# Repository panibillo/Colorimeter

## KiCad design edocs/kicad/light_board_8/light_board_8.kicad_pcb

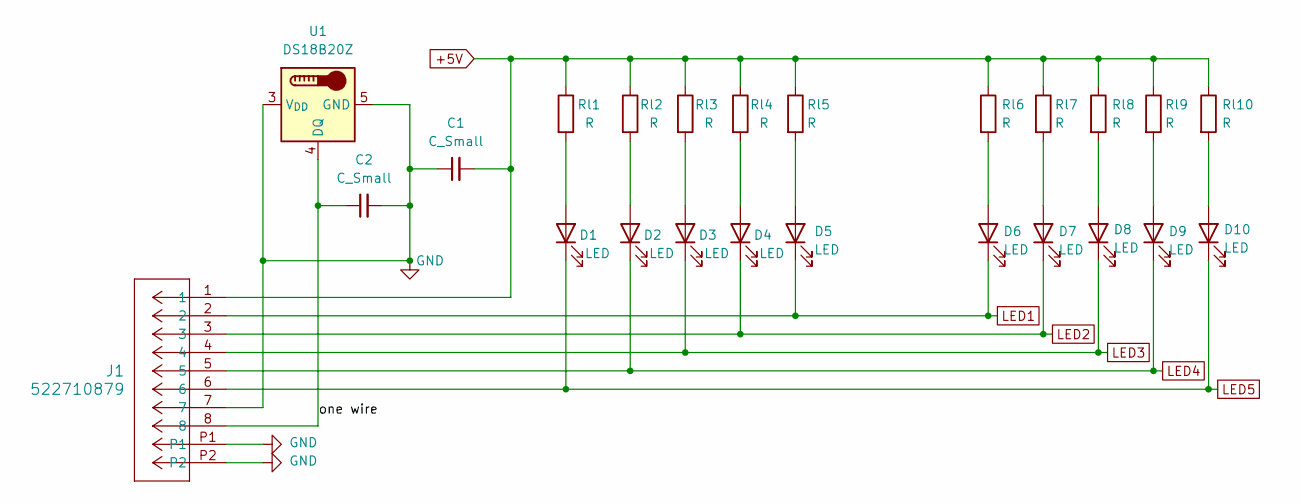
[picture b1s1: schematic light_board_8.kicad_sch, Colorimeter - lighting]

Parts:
C1: C_Small; C_0805_2012Metric
C2: C_Small; C_0603_1608Metric
D1, D2, D3, D4, D5, D6, D7, D8, D9, D10: LED; LED_PLCC_2835
J1: 522710879; CON_522710879_MOL
Rl1, Rl2, Rl3, Rl4, Rl5, Rl6, Rl7, Rl8, Rl9, Rl10: R; R_1206_3216Metric
U1: DS18B20Z; SOIC-8_3.9x4.9mm_P1.27mm

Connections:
+5V: C1.2, J1.1, Rl1.1, Rl2.1, Rl3.1, Rl4.1, Rl5.1, Rl6.1, Rl7.1, Rl8.1, Rl9.1, Rl10.1
/one wire: C2.1, J1.8, U1.4 (DQ)
GND: C1.1, C2.2, J1.7, J1.P1, J1.P2, U1.3 (V_{DD}), U1.5 (GND)
LED1: D5.1 (K), D6.1 (K), J1.2
LED2: D4.1 (K), D7.1 (K), J1.3
LED3: D3.1 (K), D8.1 (K), J1.4
LED4: D2.1 (K), D9.1 (K), J1.5
LED5: D1.1 (K), D10.1 (K), J1.6
unnamed: D1.2 (A), Rl1.2
unnamed: D2.2 (A), Rl2.2
unnamed: D3.2 (A), Rl3.2
unnamed: D4.2 (A), Rl4.2
unnamed: D5.2 (A), Rl5.2
unnamed: D6.2 (A), Rl6.2
unnamed: D7.2 (A), Rl7.2
unnamed: D8.2 (A), Rl8.2
unnamed: D9.2 (A), Rl9.2
unnamed: D10.2 (A), Rl10.2

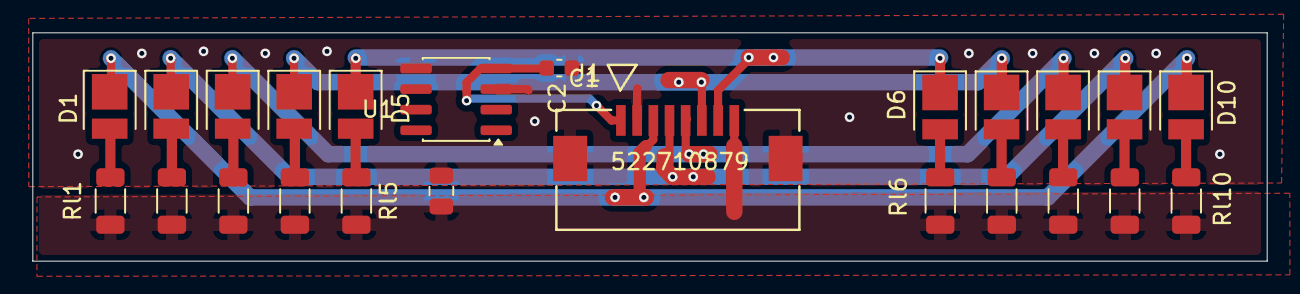
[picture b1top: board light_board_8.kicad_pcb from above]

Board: 2 copper layers, 76.2 x 14.1 mm, 24 parts (0 on the bottom side), 18 nets.

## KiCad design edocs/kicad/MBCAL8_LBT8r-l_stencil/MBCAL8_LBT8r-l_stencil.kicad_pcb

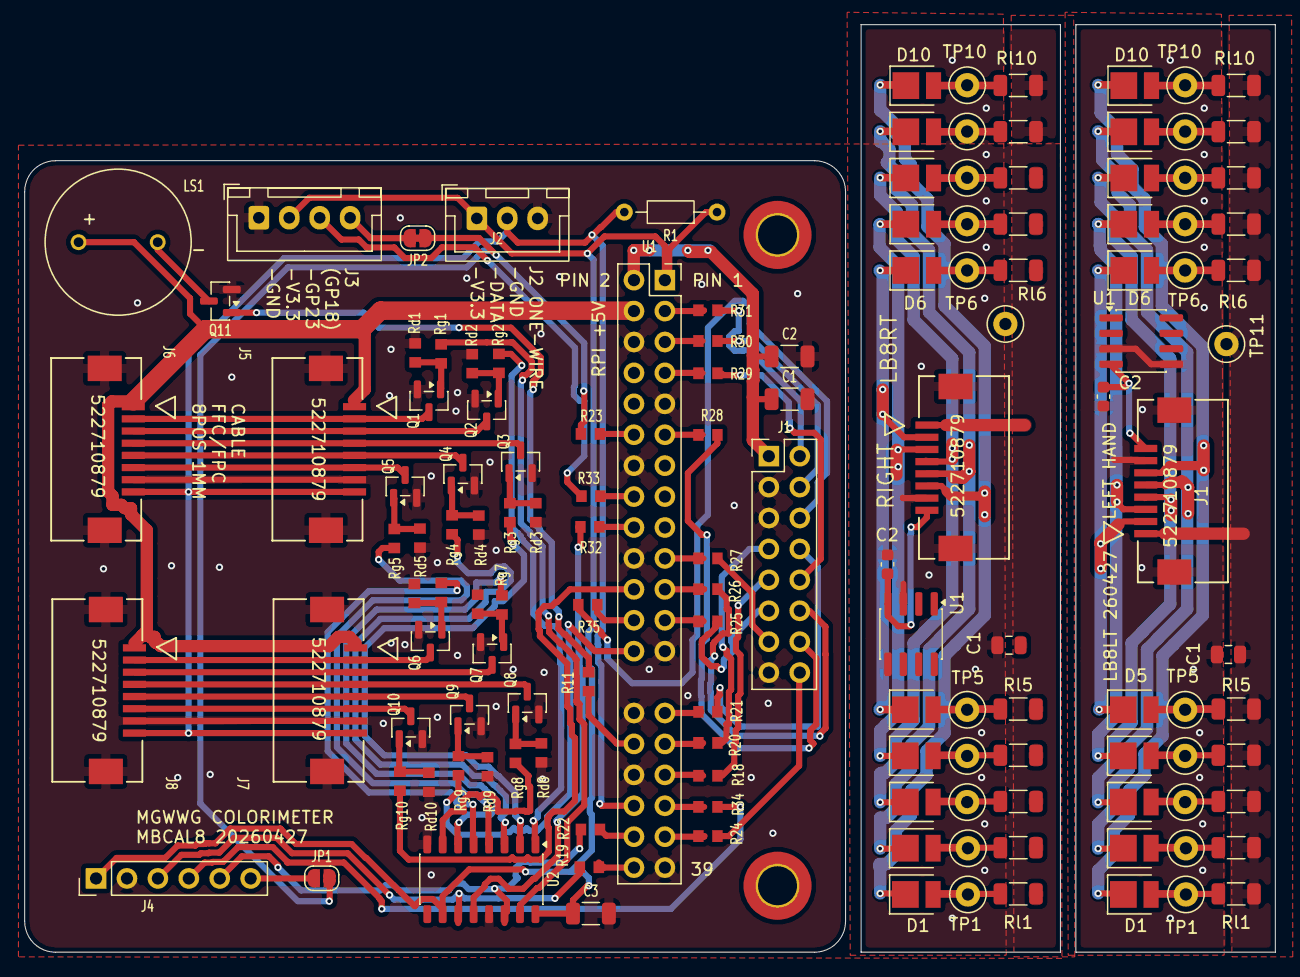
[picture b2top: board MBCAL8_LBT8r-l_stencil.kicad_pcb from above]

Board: 2 copper layers, 102.7 x 76.2 mm, 137 parts (0 on the bottom side), 87 nets.

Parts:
C1, C1#2: C_Small; C_0805_2012Metric
C1#3: 10uf Tant; C_1206_3216Metric
C2, C2#3: C_Small; C_0603_1608Metric
C2#2, C3: 100nF Ceramic; C_1206_3216Metric
D1, D1#2, D2, D2#2, D3, D3#2, D4, D4#2, D5, D5#2, D6, D6#2, D7, D7#2, D8, D8#2, D9, D9#2, D10, D10#2: LED; LED_PLCC_2835
J1: Conn_02x08_Odd_Even; PinHeader_2x08_P2.54mm_Vertical
J1#2, J1#3, J5, J6, J7, J8: 522710879; CON_522710879_MOL
J2: Conn_01x03_Socket; JST_XH_B3B-XH-A_1x03_P2.50mm_Vertical
J3: Conn_01x04_Socket; JST_XH_B4B-XH-A_1x04_P2.50mm_Vertical
J4: Conn_01x06; PinHeader_1x06_P2.54mm_Vertical
JP1: SolderJumper_2_Open; SolderJumper-2_P1.3mm_Open_RoundedPad1.0x1.5mm
JP2: SolderJumper_2_Bridged; SolderJumper-2_P1.3mm_Bridged_RoundedPad1.0x1.5mm
LS1: CEM-1203_42_; CUI_CEM-1203_42_
Q1, Q2, Q3, Q4, Q5, Q6, Q7, Q8, Q9, Q10: AO3400A; SOT-23
Q11: MMBT3904; SOT-23
R1: R_axial; R_Axial_DIN0204_L3.6mm_D1.6mm_P7.62mm_Horizontal
R11: 1K; RESC1608X55N
R18, R20, R21, R24, R25, R26, R27, R28, R29, R30, R31, R32, R33, R34, R35: R33; RESC1608X55N
R19, R22, R23: R470; RESC1608X55N
Rd1, Rd2, Rd3, Rd4, Rd5, Rd6, Rd7, Rd8, Rd9, Rd10: 10K; RESC1608X55N
Rg1, Rg2, Rg3, Rg4, Rg5, Rg6, Rg7, Rg8, Rg9, Rg10: 500; RESC1608X55N
Rl1, Rl1#2, Rl2, Rl2#2, Rl3, Rl3#2, Rl4, Rl4#2, Rl5, Rl5#2, Rl6, Rl6#2, Rl7, Rl7#2, Rl8, Rl8#2, Rl9, Rl9#2, Rl10, Rl10#2: R; R_1206_3216Metric
TP1, TP1#2, TP2, TP2#2, TP3, TP3#2, TP4, TP4#2, TP5, TP5#2, TP6, TP6#2, TP7, TP7#2, TP8, TP8#2, TP9, TP9#2, TP10, TP10#2, TP11, TP11#2: TestPoint_Small; TestPoint_Loop_D1.80mm_Drill1.0mm_Beaded
U1: RPi_Zero_W; PinSocket_2x20_P2.54mm_Vertical
U1#2, U1#3: DS18B20Z; SOIC-8_3.9x4.9mm_P1.27mm
U2: 74HC595; JEITA_SOIC-16_3.9x9.9mm_P1.27mm

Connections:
+5V: C1.2, C1#2.2, J1#2.1, J1#3.1, J5.1, J6.1, J7.1, J8.1, LS1.P, Rl1.1, Rl1#2.1, Rl2.1, Rl2#2.1, Rl3.1, Rl3#2.1, Rl4.1, Rl4#2.1, Rl5.1, Rl5#2.1, Rl6.1, Rl6#2.1, Rl7.1, Rl7#2.1, Rl8.1, Rl8#2.1, Rl9.1, Rl9#2.1, Rl10.1, Rl10#2.1, TP11.1 (1_1), TP11#2.1 (1_1), U1.4 (5V_PWR)
/Buzzer_IO: Q11.1 (B), R11.2
/D2-TSIRQ: J1.10, R29.1
/D3-LITE: J1.9, R18.1
/D4-SC CS: J1.8, R21.1
/D9-TFT DC: J1.7, R20.1
/D10-TFT CS: J1.6, R35.2
/ICSP MISO: J1.12, R26.1
/ICSP MOSI: J1.13, R27.1
/ICSP SCK: J1.11, R25.1
/SCL: J1.4, R30.1
/SDA: J1.2, R31.1
/led 1 gate: Q1.1 (G), Rd1.1, Rg1.1
/led 2 gate: Q2.1 (G), Rd2.1, Rg2.1
/led 3 GPIO: Rg3.2, U2.2 (QC)
/led 3 gate: Q3.1 (G), Rd3.1, Rg3.1
/led 4 GPIO: Rg4.2, U2.3 (QD)
/led 4 gate: Q4.1 (G), Rd4.1, Rg4.1
/led 5 GPIO: Rg5.2, U2.4 (QE)
/led 5 gate: Q5.1 (G), Rd5.1, Rg5.1
/led 6 GPIO: Rg6.2, U2.5 (QF)
/led 6 gate: Q6.1 (G), Rd6.1, Rg6.1
/led 7 GPIO: Rg7.2, U2.6 (QG)
/led 7 gate: Q7.1 (G), Rd7.1, Rg7.1
/led 8 GPIO: Rg8.2, U2.7 (QH)
/led 8 gate: Q8.1 (G), Rd8.1, Rg8.1
/led 9 GPIO: Rg9.2, U1.26 (GPIO7_CE1)
/led 9 gate: Q9.1 (G), Rd9.1, Rg9.1
/led 10 GPIO: Rg10.2, U1.22 (GPIO25)
/led 10 gate: Q10.1 (G), Rd10.1, Rg10.1
/one wire: C2.1, C2#3.1, J1#2.8, J1#3.8, U1#2.4 (DQ), U1#3.4 (DQ)
/one-wire: J2.2, J5.8, J6.8, J7.8, J8.8, R1.2, U1.36 (GPIO16_CE2)
GND: C1.1, C1#2.1, C1#3.2, C2.2, C2#2.2, C2#3.2, C3.2, J1.3, J1.5, J1.15, J1#2.7, J1#2.P1, J1#2.P2, J1#3.7, J1#3.P1, J1#3.P2, J2.3, J3.1, J4.2, J5.7, J5.P1, J5.P2, J6.7, J6.P1, J6.P2, J7.7, J7.P1, J7.P2, J8.7, J8.P1, J8.P2, Q1.2 (S), Q2.2 (S), Q3.2 (S), Q4.2 (S), Q5.2 (S), Q6.2 (S), Q7.2 (S), Q8.2 (S), Q9.2 (S), Q10.2 (S), Q11.2 (E), Rd1.2, Rd2.2, Rd3.2, Rd4.2, Rd5.2, Rd6.2, Rd7.2, Rd8.2, Rd9.2, Rd10.2, U1.6 (GND), U1.9 (GND), U1.14 (GND), U1.20 (GND), U1.25 (GND), U1.30 (GND), U1.34 (GND), U1.39 (GND), U1#2.3 (V_{DD}), U1#2.5 (GND), U1#3.3 (V_{DD}), U1#3.5 (GND), U2.8 (GND), U2.13 (~OE)
LED1: D5.1 (K), D5#2.1 (K), D6.1 (K), D6#2.1 (K), J1#2.2, J1#3.2, J5.2, J6.2, Q1.3 (D)
LED2: D4.1 (K), D4#2.1 (K), D7.1 (K), D7#2.1 (K), J1#2.3, J1#3.3, J5.3, J6.3, Q2.3 (D)
LED3: D3.1 (K), D3#2.1 (K), D8.1 (K), D8#2.1 (K), J1#2.4, J1#3.4, J5.4, J6.4, Q3.3 (D)
LED4: D2.1 (K), D2#2.1 (K), D9.1 (K), D9#2.1 (K), J1#2.5, J1#3.5, J5.5, J6.5, Q4.3 (D)
LED5: D1.1 (K), D1#2.1 (K), D10.1 (K), D10#2.1 (K), J1#2.6, J1#3.6, J5.6, J6.6, Q5.3 (D)
LED6: J7.2, J8.2, Q6.3 (D)
LED7: J7.3, J8.3, Q7.3 (D)
LED8: J7.4, J8.4, Q8.3 (D)
LED9: J7.5, J8.5, Q9.3 (D)
LED10: J7.6, J8.6, Q10.3 (D)
unnamed: D1.2 (A), D1#2.2 (A), Rl1.2, Rl1#2.2, TP1.1 (1_1), TP1#2.1 (1_1)
unnamed: D2.2 (A), D2#2.2 (A), Rl2.2, Rl2#2.2, TP2.1 (1_1), TP2#2.1 (1_1)
unnamed: D3.2 (A), D3#2.2 (A), Rl3.2, Rl3#2.2, TP3.1 (1_1), TP3#2.1 (1_1)
unnamed: D4.2 (A), D4#2.2 (A), Rl4.2, Rl4#2.2, TP4.1 (1_1), TP4#2.1 (1_1)
unnamed: D5.2 (A), D5#2.2 (A), Rl5.2, Rl5#2.2, TP5.1 (1_1), TP5#2.1 (1_1)
unnamed: D6.2 (A), D6#2.2 (A), Rl6.2, Rl6#2.2, TP6.1 (1_1), TP6#2.1 (1_1)
unnamed: D7.2 (A), D7#2.2 (A), Rl7.2, Rl7#2.2, TP7.1 (1_1), TP7#2.1 (1_1)
unnamed: D8.2 (A), D8#2.2 (A), Rl8.2, Rl8#2.2, TP8.1 (1_1), TP8#2.1 (1_1)
unnamed: D9.2 (A), D9#2.2 (A), Rl9.2, Rl9#2.2, TP9.1 (1_1), TP9#2.1 (1_1)
unnamed: D10.2 (A), D10#2.2 (A), Rl10.2, Rl10#2.2, TP10.1 (1_1), TP10#2.1 (1_1)
unnamed: C1#3.1, C2#2.1, J1.1, U1.2 (5V_PWR)
unnamed: J1.14, R28.1
unnamed: J1.16, R24.1
unnamed: J3.3, R33.2
unnamed: J3.4, JP2.2 (B)
unnamed: J4.3, R19.2, U2.11 (SRCLK)
unnamed: J4.4, R34.1
unnamed: J4.5, R22.2, U2.14 (SER)
unnamed: J4.6, JP1.1 (A)
unnamed: JP1.2 (B), JP2.1 (A), R23.2
unnamed: LS1.N, Q11.3 (C)
unnamed: R31.2, U1.3 (GPIO2_SDA1)
unnamed: R30.2, U1.5 (GPIO3_SCL1)
unnamed: R29.2, U1.7 (GPIO4_GPCLK0)
unnamed: R21.2, U1.29 (GPIO5)
unnamed: R20.2, U1.31 (GPIO6)
unnamed: R35.1, U1.24 (GPIO8_CE0)
unnamed: R26.2, U1.21 (GPIO9_MISO)
unnamed: R27.2, U1.19 (GPIO10_MOSI)
unnamed: R25.2, U1.23 (GPIO11_SCLK)
unnamed: R11.1, U1.32 (GPIO12_PWM0)
unnamed: R18.2, U1.33 (GPIO13_PWM1)
unnamed: R28.2, U1.11 (GPIO17)
unnamed: R23.1, U1.12 (GPIO18_PCM_CLK)
unnamed: R34.2, U1.35 (GPIO19_MISO1)
unnamed: R22.1, U1.38 (GPIO20_MOSI1)
unnamed: R19.1, U1.40 (GPIO21_SCLK1)
unnamed: R33.1, U1.16 (GPIO23)
unnamed: R32.1, U1.18 (GPIO24)
unnamed: R24.2, U1.37 (GPIO26)
unnamed: Rg1.2, U2.15 (QA)
unnamed: Rg2.2, U2.1 (QB)
unnamed: R32.2, U2.12 (RCLK)
V3.3: C3.1, J2.1, J3.2, J4.1, R1.1, U1.1 (3V3_PWR), U2.10 (~SRCLR), U2.16 (VCC)

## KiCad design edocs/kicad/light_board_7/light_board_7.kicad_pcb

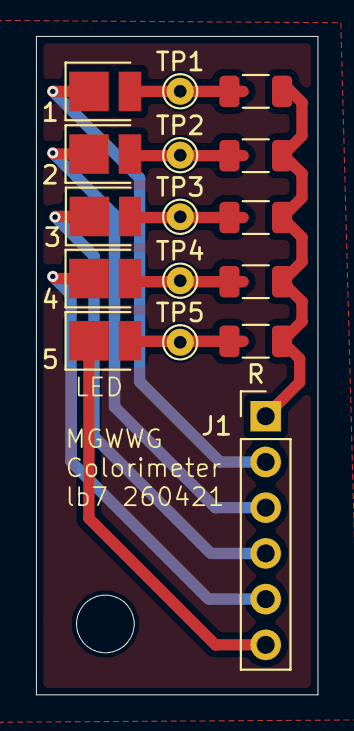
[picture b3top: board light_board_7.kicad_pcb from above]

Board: 2 copper layers, 15.6 x 36.6 mm, 16 parts (0 on the bottom side), 11 nets.

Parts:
1, 2, 3, 4, 5: LED; LED_PLCC_2835
J1: Conn_01x06; PinHeader_1x06_P2.54mm_Vertical
R, R1, R2, R3, R4: R; R_1206_3216Metric
TP1, TP2, TP3, TP4, TP5: TestPoint_Small; TestPoint_THTPad_D1.5mm_Drill0.7mm

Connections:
+5V: J1.1, R.1, R1.1, R2.1, R3.1, R4.1
LED1: 1.1 (K), J1.2
LED2: 2.1 (K), J1.3
LED3: 3.1 (K), J1.4
LED4: 4.1 (K), J1.5
LED5: 5.1 (K), J1.6
unnamed: 1.2 (A), R1.2, TP1.1 (1_1)
unnamed: 2.2 (A), R2.2, TP2.1 (1_1)
unnamed: 3.2 (A), R3.2, TP3.1 (1_1)
unnamed: 4.2 (A), R4.2, TP4.1 (1_1)
unnamed: 5.2 (A), R.2, TP5.1 (1_1)

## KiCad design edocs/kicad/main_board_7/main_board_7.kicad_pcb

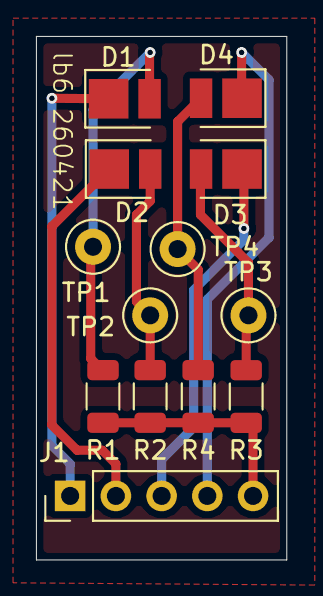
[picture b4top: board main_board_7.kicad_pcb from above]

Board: 2 copper layers, 13.9 x 29.1 mm, 13 parts (0 on the bottom side), 9 nets.

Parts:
D1, D2, D3, D4: LED; LED_PLCC_2835
J1: Conn_01x05; PinHeader_1x05_P2.54mm_Vertical
R1, R2, R3, R4: R; R_1206_3216Metric
TP1, TP2, TP3, TP4: TestPoint_Small; TestPoint_Loop_D1.80mm_Drill1.0mm_Beaded

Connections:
+5V: J1.5, R1.1, R2.1, R3.1, R4.1
/J1: D1.1 (K), J1.1
/J2: D2.1 (K), J1.2
/J3: D3.1 (K), J1.3
/J4: D4.1 (K), J1.4
unnamed: D1.2 (A), R1.2, TP1.1 (1_1)
unnamed: D2.2 (A), R2.2, TP2.2 (1_1)
unnamed: D3.2 (A), R3.2
unnamed: D4.2 (A), R4.2

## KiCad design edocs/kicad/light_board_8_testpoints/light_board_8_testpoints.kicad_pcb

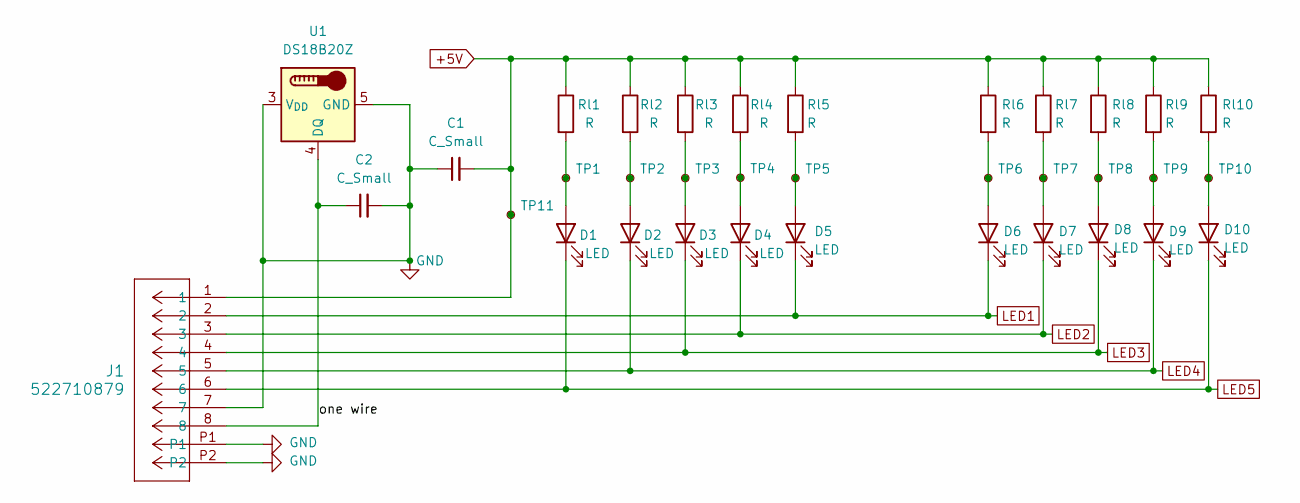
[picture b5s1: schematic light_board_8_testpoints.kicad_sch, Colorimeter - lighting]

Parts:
C1: C_Small; C_0805_2012Metric
C2: C_Small; C_0603_1608Metric
D1, D2, D3, D4, D5, D6, D7, D8, D9, D10: LED; LED_PLCC_2835
J1: 522710879; CON_522710879_MOL
Rl1, Rl2, Rl3, Rl4, Rl5, Rl6, Rl7, Rl8, Rl9, Rl10: R; R_1206_3216Metric
TP1, TP2, TP3, TP4, TP5, TP6, TP7, TP8, TP9, TP10, TP11: TestPoint_Small; TestPoint_Loop_D1.80mm_Drill1.0mm_Beaded
U1: DS18B20Z; SOIC-8_3.9x4.9mm_P1.27mm

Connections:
+5V: C1.2, J1.1, Rl1.1, Rl2.1, Rl3.1, Rl4.1, Rl5.1, Rl6.1, Rl7.1, Rl8.1, Rl9.1, Rl10.1, TP11.1 (1_1)
/one wire: C2.1, J1.8, U1.4 (DQ)
GND: C1.1, C2.2, J1.7, J1.P1, J1.P2, U1.3 (V_{DD}), U1.5 (GND)
LED1: D5.1 (K), D6.1 (K), J1.2
LED2: D4.1 (K), D7.1 (K), J1.3
LED3: D3.1 (K), D8.1 (K), J1.4
LED4: D2.1 (K), D9.1 (K), J1.5
LED5: D1.1 (K), D10.1 (K), J1.6
unnamed: D1.2 (A), Rl1.2, TP1.1 (1_1)
unnamed: D2.2 (A), Rl2.2, TP2.1 (1_1)
unnamed: D3.2 (A), Rl3.2, TP3.1 (1_1)
unnamed: D4.2 (A), Rl4.2, TP4.1 (1_1)
unnamed: D5.2 (A), Rl5.2, TP5.1 (1_1)
unnamed: D6.2 (A), Rl6.2, TP6.1 (1_1)
unnamed: D7.2 (A), Rl7.2, TP7.1 (1_1)
unnamed: D8.2 (A), Rl8.2, TP8.1 (1_1)
unnamed: D9.2 (A), Rl9.2, TP9.1 (1_1)
unnamed: D10.2 (A), Rl10.2, TP10.1 (1_1)

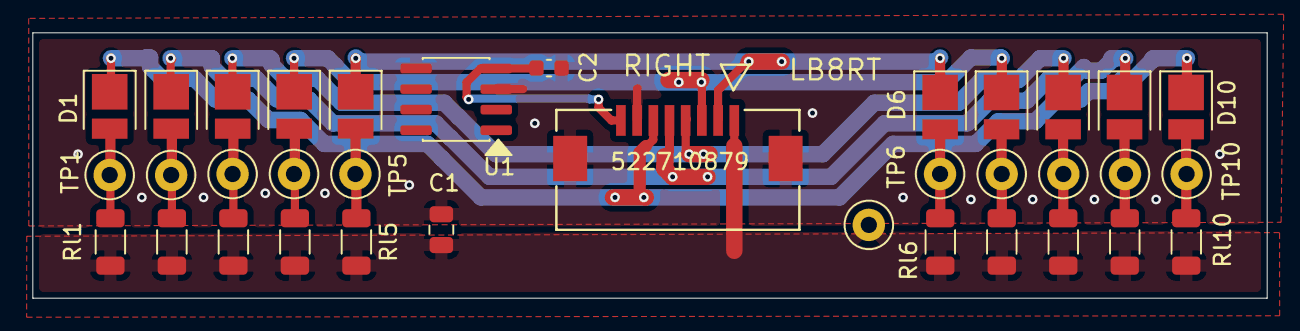
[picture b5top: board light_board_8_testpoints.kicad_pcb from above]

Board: 2 copper layers, 76.2 x 16.4 mm, 35 parts (0 on the bottom side), 18 nets.

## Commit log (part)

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2026-03-07 First commit. Just testing the camera
2026-03-07 Works: added automatic exposure. 2 unused methods to decode & wb bayer.
2026-03-09 camtest1 to 3 work, though 3 is not all tested
2026-03-10 working on figuring out unpacking of Bayer images
2026-03-11 Now saving unpacked bayer (16bit). visual check with test_bayer_display()
2026-03-12 Added test/*.py, early versions of src/*.py, most .md
2026-03-21 Create new class Rect in rect.py, with test module. - works
2026-03-22 Fixed exposure limit and exposure calc in camtest5.py
2026-03-22 Continuing search for longer exposure with camtest5 and camtest6. Final attempt?
2026-03-22 Begin find_rects.py. Finds all rects in 5x7 grid, but bounds need better adjusting.
2026-03-22 find_rects.py works but imperfect. CLI args: -s 0.7 -b 10 Then manual edit rects.
2026-03-25 Bayer captures are wrong in most units. Fixed in src/color_cam.py (but other methods are stale.)
2026-03-25 Renaming: color_cam.py to bayer_cam.py, and class ColorCam to BayerCam
2026-04-04 Added -l option to camtest5. Refactored camtest to use src/lighting. New dev/lighttest interactive lighting control
2026-04-10 first web interface in dev. for design tasks
2026-04-14 working on first web interface
2026-04-14 bayer_cam modified to include focus information for Camera Module 3
2026-04-14 webtest2 first version
2026-04-16 new methods for analyzing LED lighting test results
2026-05-20 storing legacy files in current state. Before adding recent work.
2026-05-21 restored Narrative.md
2026-05-21 added 1651 display dev units and 1st untested libraries
2026-05-27 Pretty functional touchscreen display
2026-05-28 most camera tests working
2026-05-28 version 0.1 of lab_instrument_spec.
2026-05-30 fixed bayer_cam Py Camera Module 3 processing.
2026-05-30 Added full resolution and draw roi rect to test_cam_display. cleaned up debugs
2026-05-30 add desktop/ dir for the desktop side scripts. New upload method examined
